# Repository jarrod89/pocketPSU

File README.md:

# pocketPSU

## Specs  
Output1:  
- Efuse protected USBPD output
- 3A, 20V 
- setting resolution depends on capability of USB-C brickw. If using a PPS capable supply, 10mV CV and 50mA CC settings
- By default this output is disabled as the PD command will track output 3 for minimal power loss in LDO
- Must be lower than output2  
  
Input1:
- Output1 can be used to supply pocketPSU via a battery
- Optional battery charging capability (addon board with BMS)
  
Output2:  
- (optional) Boost output with efuse protection (no dedicated CC)
- 1A 3.3-30V
- By default this tracks output3 for minimal power loss in LDO
- Must be higher than output1 and output3

Output3:  
- LDO output for low ripple
- 1A 0-30V (limited current based on input/output delta)
- Must be lower than output1

### User interface

The user interface will consist of:

- One LCD screen
- One rotary encode + integrated switch. The switch could serve as a way to switch between fine and coarse setting
- One button to turn the power output on/off
- Three buttons for navigation:
  - Up
  - Down
  - Select

### Powering the PSU

The supply can be powered over USB-C or using an external battery. The battery could potentially be a power tool battery that users already have on hand.

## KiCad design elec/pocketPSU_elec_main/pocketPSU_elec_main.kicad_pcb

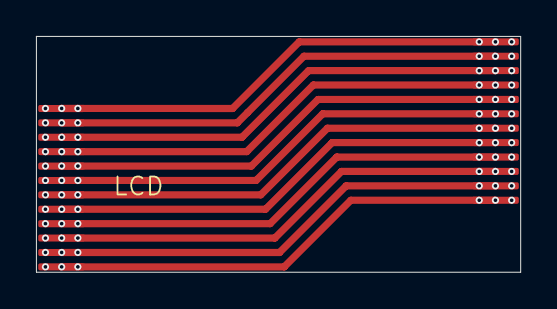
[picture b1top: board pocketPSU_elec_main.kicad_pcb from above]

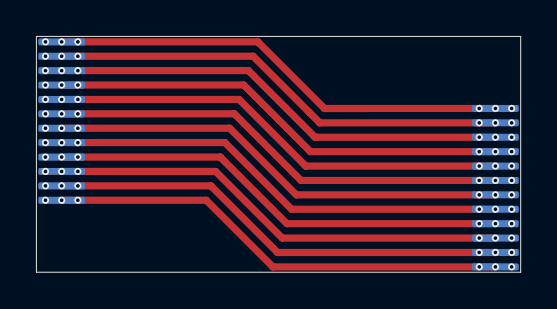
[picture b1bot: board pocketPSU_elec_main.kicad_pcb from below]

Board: 2 copper layers, 26.9 x 13.1 mm, 4 parts (2 on the bottom side), 12 nets.

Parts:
J1, J2, J3, J4: Conn_01x12_Pin; LCD-GMT020-02

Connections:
unnamed: J1.1, J2.1, J3.1, J4.1
unnamed: J1.2, J2.2, J3.2, J4.2
unnamed: J1.3, J2.3, J3.3, J4.3
unnamed: J1.4, J2.4, J3.4, J4.4
unnamed: J1.5, J2.5, J3.5, J4.5
unnamed: J1.6, J2.6, J3.6, J4.6
unnamed: J1.7, J2.7, J3.7, J4.7
unnamed: J1.8, J2.8, J3.8, J4.8
unnamed: J1.9, J2.9, J3.9, J4.9
unnamed: J1.10, J2.10, J3.10, J4.10
unnamed: J1.11, J2.11, J3.11, J4.11
unnamed: J1.12, J2.12, J3.12, J4.12

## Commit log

2024-08-07 add some specs
2024-08-07 add early electrical architecture
2024-08-07 add gitignore
2024-08-07 part selection spreadsheet
2024-08-08 added user interface elements
2024-08-08 add button, deglitch
2024-08-08 lad into layout
2024-08-08 update requirements
2024-08-08 add value to bypass cap
2024-08-09 update gitignore
2024-08-09 add esp32 micro
2024-08-10 Add footprints, change TFT hookup
2024-08-10 preliminary layout
2024-08-13 add usb coms chip
2024-08-13 add bypass caps on usb coms chip
2024-08-13 fix caps values, rework layout
2024-08-13 add copper fill
2024-08-13 route traces and add gnd pour
2024-08-14 add boot switch and test points
2024-08-17 ldo circuit + simulation
2024-08-18 tuning for better response
2024-08-19 add buttons and leds for on/off indication
2024-08-23 move components, add mounting holes
2024-09-01 move pullup nodes, change to 2.54mm header
2024-09-01 board routed
2024-09-01 add groud vias
2024-09-01 fix some drcs
2024-09-01 fix schematic
2024-09-05 mid-layout
2024-09-06 finished routing
2024-09-06 kibot quickstart
2024-09-06 fixing 3d models
2024-09-06 use a kibot config
2024-09-06 add jlc config
2024-09-06 try fixing actions file
2024-09-06 test changing kibot file, should trigger an action
2024-09-06 add paths to schematic and pcb
2024-09-06 dont run erc
2024-09-06 remove some kibot garbage
2024-09-06 add path
2024-09-06 use builtin jlcpcb config
2024-09-06 add cache
2024-09-06 add cache again
2024-09-06 add back local jlcpcb config
2024-09-06 variant problem
2024-09-06 filter fix
2024-09-06 fix jlc bom
2024-09-06 renaming
2024-09-06 typo in ibom option
2024-09-07 Kibot (#7)
    Add kibot with JLC output generation
2024-09-07 fix 3d, add drc
2024-09-08 fix erc
2024-09-08 fix pcb drc
2024-09-08 drc ignore_unconnected
2024-09-11 attempt to add githash and tag
2024-09-11 add silk githash string
2024-09-11 add silk tag string
2024-09-11 change outputs
2024-09-11 Cleanup, Buck, CAN (#6)
    * mid-layout
    * finished routing
    * Kibot (#7)
    Add kibot with JLC output generation
    * fix 3d, add drc
    * fix erc
2024-09-11 remove 3d and pcb prints
2024-09-11 ctrl-z
2024-09-11 clean up kibot
2024-09-11 add 3d render
2024-09-11 add 3d render and make it run
2024-09-11 fix kibot (#8)
    * remove 3d and pcb prints
    * ctrl-z
    * clean up kibot
    * add 3d render
    * add 3d render and make it run
    ---------
2024-09-12 Add mini esp32 module, smd rotary encoder and leds
2024-09-12 add erc flags to unconnected pins
2024-09-12 fix DRC errors (#9)
    * nop
    * add erc flags to unconnected pins
    ---------
2024-09-13 add platformio project with lcd demo
2024-09-18 wip: add config for rp2040 with basic state machine
2024-09-19 add blinky debug, memory csv and comment out pico build
2024-09-19 make flex pcb for lcd fix
2024-09-19 change to build on sch change
2024-09-19 change to build on push
2024-09-19 change to build on push1
2024-09-19 play with encoder library
2024-09-20 manual interrupt based encoder logic. fun meter on LCD
2024-09-20 moved pin definitions to platformio.ini so it compiles on pico again
2024-09-29 play with lvgl
2024-09-29 "deep+" option to resolve dependency graph was causing issues. Switched to "deep"
2024-09-29 shuffling values on screen + cleanup
2024-09-29 remove printf
2024-10-01 bricked
2024-10-06 first stab at usb coms
2024-10-11 checkpoint
2024-10-12 move to platformio library for fusb302, use uart0 for debug
2024-10-13 9v output
2024-10-13 fix logging
2024-10-13 Esp fw (#10)
    * nop
    * add erc flags to unconnected pins
    * add platformio project with lcd demo
    * wip: add config for rp2040 with basic state machine
    * add blinky debug, memory csv and comment out pico build
    * play with encoder library
2024-10-15 add debugging
2024-10-15 builds again
